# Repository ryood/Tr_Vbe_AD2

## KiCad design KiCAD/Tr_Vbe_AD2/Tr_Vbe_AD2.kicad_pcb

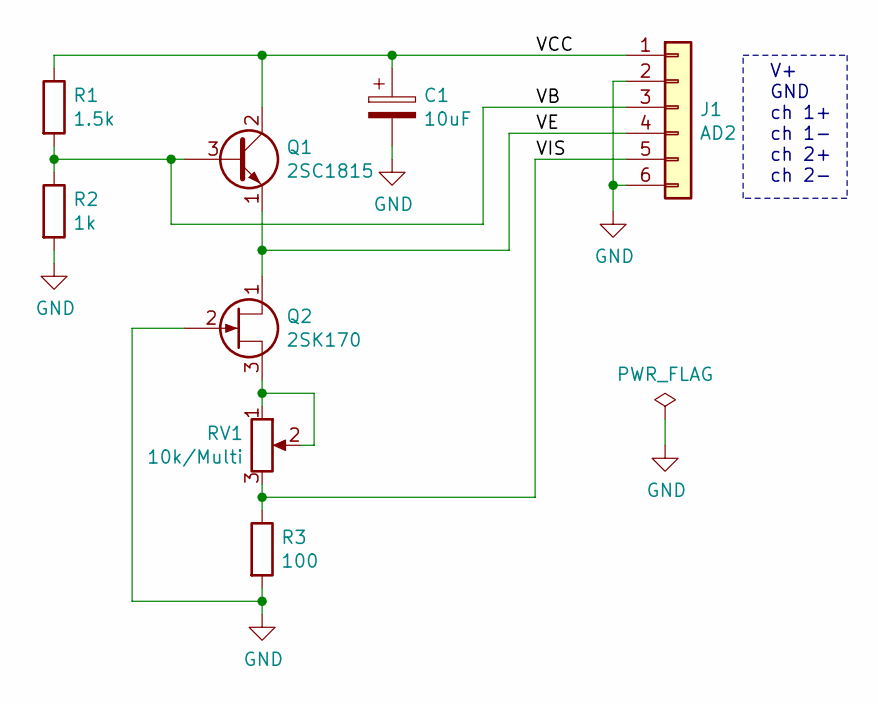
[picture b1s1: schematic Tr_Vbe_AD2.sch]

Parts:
C1: 10uF; CP_Radial_D5.0mm_P2.50mm
J1: AD2; PinSocket_1x06_P2.54mm_Vertical
Q1: 2SC1815; TO-92L_Inline_Wide
Q2: 2SK170; TO-92_Wide
R1: 1.5k; R_Axial_DIN0207_L6.3mm_D2.5mm_P7.62mm_Horizontal
R2: 1k; R_Axial_DIN0207_L6.3mm_D2.5mm_P7.62mm_Horizontal
R3: 100; R_Axial_DIN0207_L6.3mm_D2.5mm_P7.62mm_Horizontal
RV1: 10k/Multi; Potentiometer_Bourns_3296W_Vertical

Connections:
/VB: J1.3, Q1.3 (B), R1.2, R2.1
/VCC: C1.1, J1.1, Q1.2 (C), R1.1
/VE: J1.4, Q1.1 (E), Q2.1 (D)
/VIS: J1.5, R3.1, RV1.3
GND: C1.2, J1.2, J1.6, Q2.2 (G), R2.2, R3.2
unnamed: Q2.3 (S), RV1.1, RV1.2

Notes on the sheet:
V+ GND ch 1+ ch 1- ch 2+ ch 2-

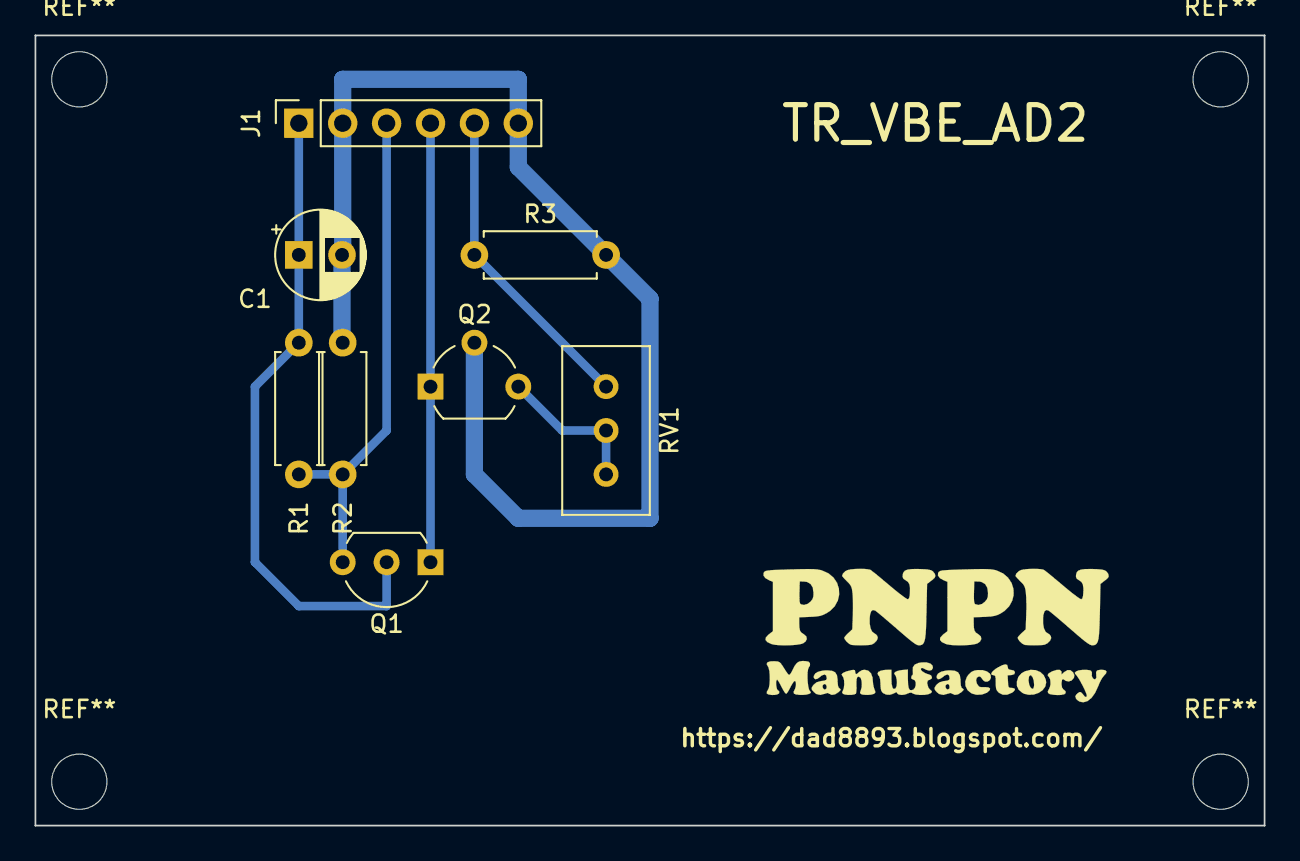
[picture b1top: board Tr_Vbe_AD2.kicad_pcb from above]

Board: 2 copper layers, 71.1 x 45.7 mm, 8 parts (0 on the bottom side), 6 nets.

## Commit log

2020-08-09 Add files
2020-08-11 Update: Board design
